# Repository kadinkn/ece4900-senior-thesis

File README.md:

# ECE4900 Floating Photovoltaic Power System

Senior Thesis project focused on designing and testing a small-scale floating photovoltaic power system with:

- Custom synchronous buck converter
- MPPT control
- STM32G474 microcontroller
- PV and battery voltage/current sensing
- Temperature sensing
- Real-time UART telemetry
- Input and output protection
- Battery charging interface

## Project Status

Current work includes:

- Buck converter power stage
- Gate driver circuitry
- 12 V auxiliary supply
- 3.3 V MCU supply
- STM32 support circuitry
- SWD programming/debug interface
- PWM control connections
- PV voltage/current sensing
- Battery voltage/current sensing
- Temperature sensing
- UART telemetry
- PV input protection
- Battery output protection

PCB layout, design-rule checks, manufacturing files, firmware, and hardware testing are still in progress.

## Main Hardware

- MCU: STM32G474CBT6TR
- Gate Driver: TI UCC27301A
- Buck MOSFETs: TI CSD18540Q5B
- PV Panel: Renogy 100 W
- Battery: Renogy 12.8 V 20 Ah LiFePO4

## Repository Files

Open the `.kicad_pro` file in KiCad to load the project.

The repository will eventually contain:

- KiCad schematic
- PCB layout
- BOM
- Datasheets/reference documents
- Manufacturing files
- Firmware
- Testing documentation

## Notes

This is a Rev 0 prototype design and is still under active development and review.

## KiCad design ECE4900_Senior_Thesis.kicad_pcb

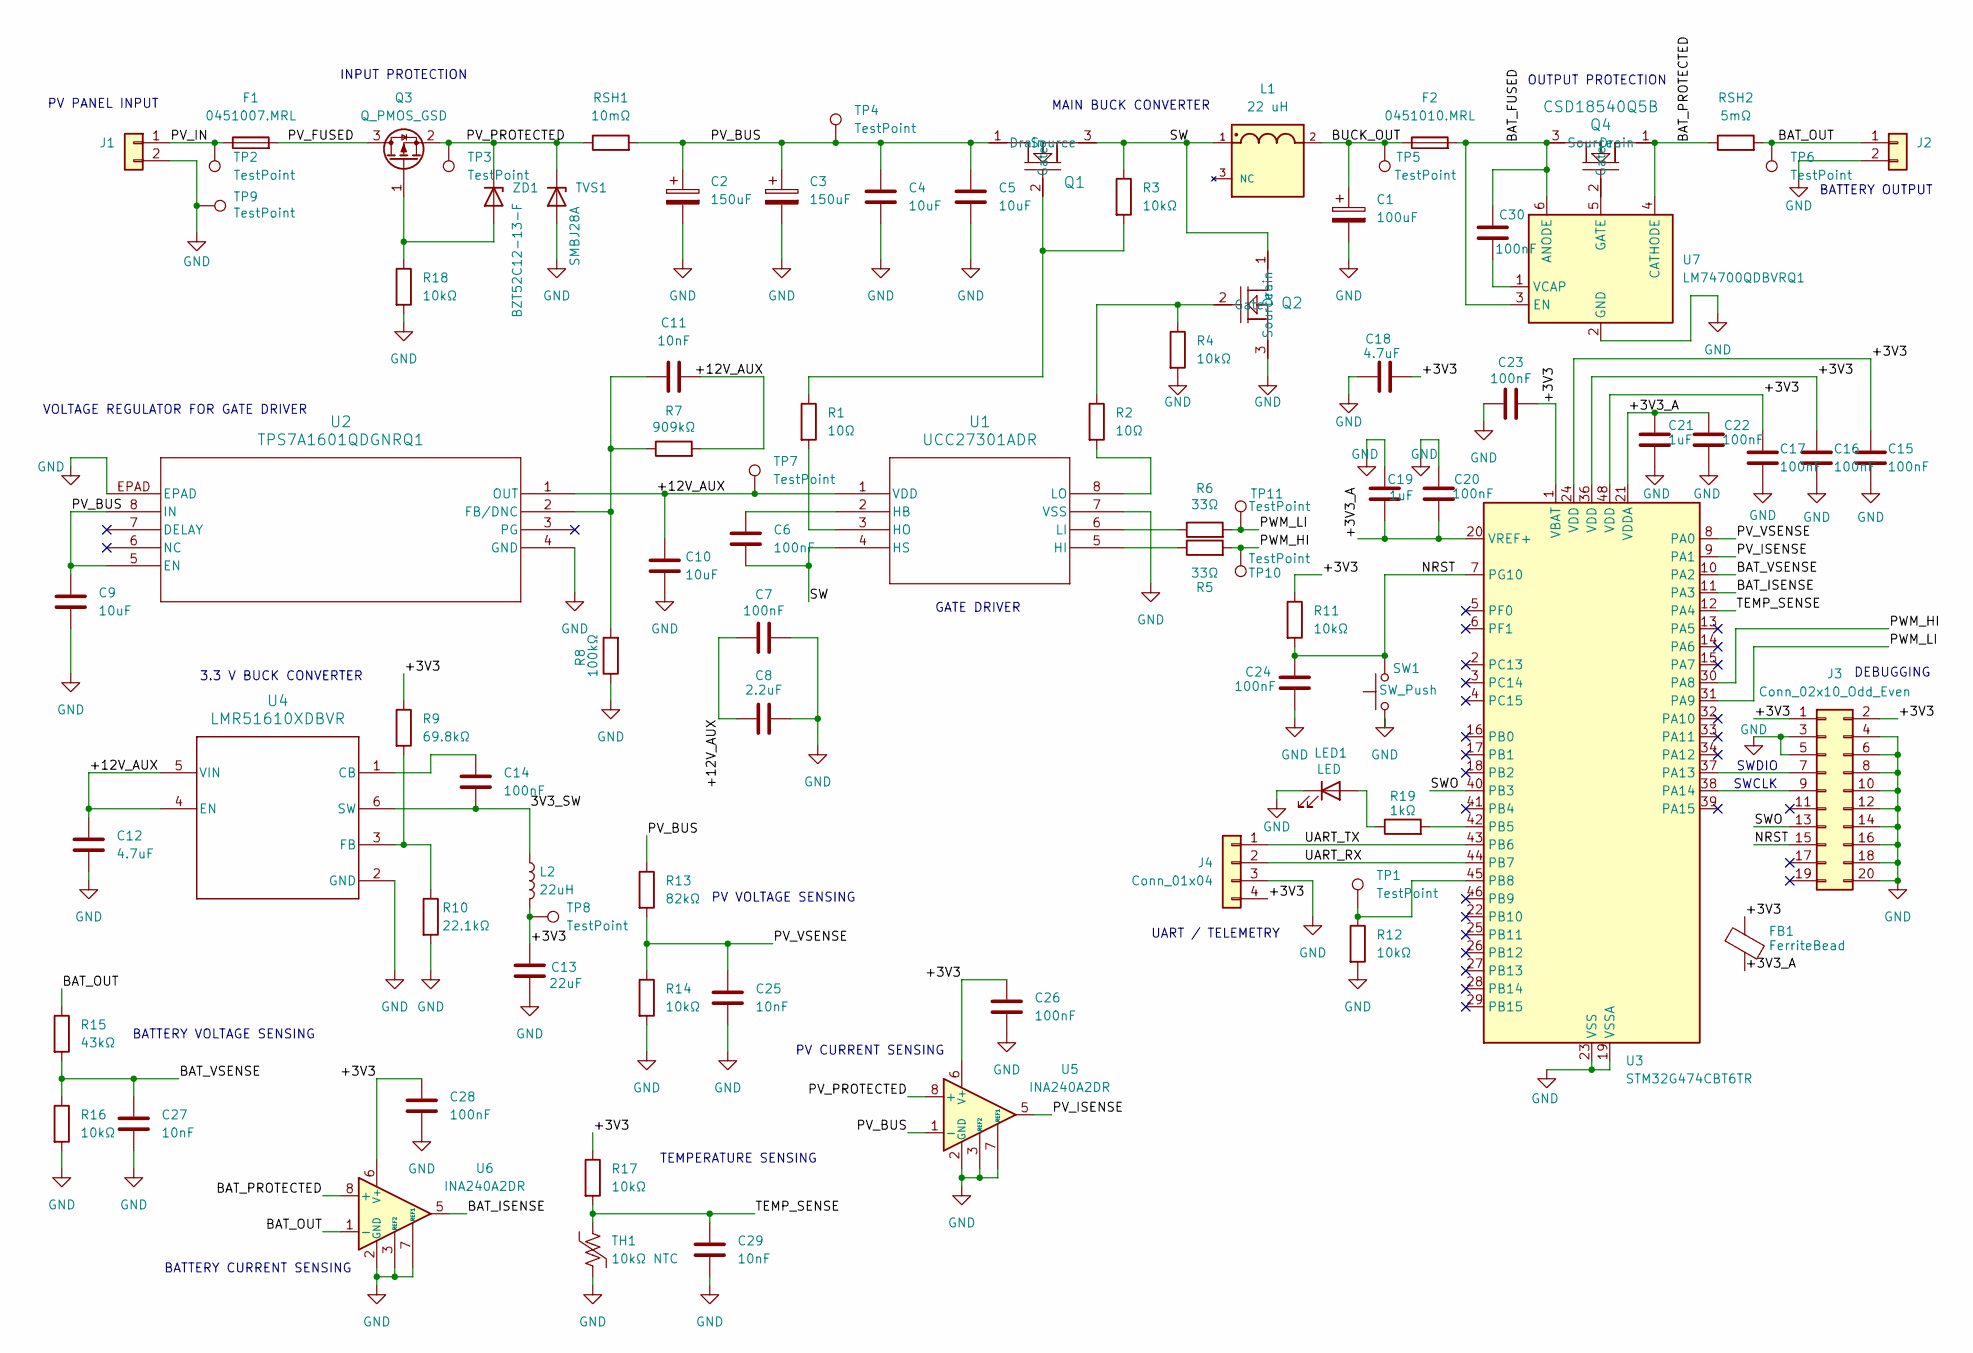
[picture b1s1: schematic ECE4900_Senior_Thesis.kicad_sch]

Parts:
C1: 100uF; CP_Elec_8x6.9
C2, C3: 150uF; CP_Elec_10x12.5
C4, C5, C9, C10: 10uF; C_1210_3225Metric
C6, C7, C14, C15, C16, C17, C20, C22, C23, C24, C26, C28, C30: 100nF; C_0603_1608Metric
C8: 2.2uF; C_0805_2012Metric
C11, C25, C27, C29: 10nF; C_0603_1608Metric
C12: 4.7uF; C_1206_3216Metric
C13: 22uF; C_1210_3225Metric
C18: 4.7uF; C_0805_2012Metric
C19, C21: 1uF; C_0603_1608Metric
F1: 0451007.MRL; Fuse_Littelfuse-NANO2-451_453
F2: 0451010.MRL; Fuse_Littelfuse-NANO2-451_453
FB1: FerriteBead; L_0603_1608Metric
J1, J2: 1757242; PhoenixContact_MSTBA_2,5_2-G-5,08_1x02_P5.08mm_Horizontal
J3: Conn_02x10_Odd_Even; IDC-Header_2x10_P2.54mm_Vertical
J4: Conn_01x04; PinHeader_1x04_P2.54mm_Vertical
L1: 22 uH; CSCF2014-220MC; PARTREV 05/31/2024
L2: 22uH; IND_1273AS-H-220M=P3
LED1: LED; LED_0603_1608Metric
Q1, Q2, Q4: CSD18540Q5B
Q3: Q_PMOS_GSD; Diodes_PowerDI3333-8
R1, R2: 10Ω; R_0805_2012Metric
R3, R4, R11, R12, R14, R16, R17, R18: 10kΩ; R_0603_1608Metric
R5, R6: 33Ω; R_0603_1608Metric
R7: 909kΩ; R_0603_1608Metric
R8: 100kΩ; R_0603_1608Metric
R9: 69.8kΩ; R_0603_1608Metric
R10: 22.1kΩ; R_0603_1608Metric
R13: 82kΩ; R_0603_1608Metric
R15: 43kΩ; R_0603_1608Metric
R19: 1kΩ; R_0603_1608Metric
RSH1: 10mΩ; KRL3264E-C-R010-F-T1
RSH2: 5mΩ; RESC6432X90N
SW1: SW_Push; SW_PUSH_6mm_H4.3mm
TH1: 10kΩ NTC; R_0603_1608Metric
TP1, TP2, TP3, TP4, TP5, TP6, TP7, TP8, TP9, TP10, TP11: TestPoint; TestPoint_Keystone_5000-5004_Miniature
TVS1: SMBJ28A; D_SMB
U1: UCC27301ADR
U2: TPS7A1601QDGNRQ1; DGN8_1P92X1P6_TEX
U3: STM32G474CBT6TR; LQFP-48_7x7mm_P0.5mm
U4: LMR51610XDBVR; DBV0006A-IPC_A
U5, U6: INA240A2DR; SOIC-8_3.9x4.9mm_P1.27mm
U7: LM74700QDBVRQ1; SOT-23-6
ZD1: BZT52C12-13-F; D_SOD-123

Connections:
/3V3_SW: C14.2, L2.1, U4.6 (SW)
/+3V3: C13.1, C15.1, C16.1, C17.1, C18.2, C23.2, C26.1, C28.1, FB1.1, J3.1, J3.2, J4.4, L2.2, R9.1, R11.1, R17.1, TP8.1 (1_1), U3.1 (VBAT), U3.24 (VDD), U3.36 (VDD), U3.48 (VDD), U5.6 (V+), U6.6 (V+)
/+3V3_A: C19.2, C20.2, C21.1, C22.1, FB1.2, U3.20 (VREF+), U3.21 (VDDA)
/+12V_AUX: C7.1, C8.1, C10.1, C11.2, C12.1, R7.2, TP7.1 (1_1), U1.1 (VDD), U2.1 (OUT), U4.4 (EN), U4.5 (VIN)
/BAT_FUSED: C30.1, F2.2, Q4.3 (Source), U7.3 (EN), U7.6 (ANODE)
/BAT_ISENSE: U3.11 (PA3), U6.5
/BAT_OUT: J2.1, R15.1, RSH2.2, TP6.1 (1_1), U6.1 (-)
/BAT_PROTECTED: Q4.1 (Drain), RSH2.1, U6.8 (+), U7.4 (CATHODE)
/BAT_VSENSE: C27.1, R15.2, R16.1, U3.10 (PA2)
/BUCK_OUT: C1.1, F2.1, L1.2, TP5.1 (1_1)
/NRST: C24.1, J3.15, R11.2, SW1.2, U3.7 (PG10)
/PV_BUS: C2.1, C3.1, C4.1, C5.1, C9.1, Q1.1 (Drain), R13.1, RSH1.2, TP4.1 (1_1), U2.5 (EN), U2.8 (IN), U5.1 (-)
/PV_FUSED: F1.2, Q3.3 (D)
/PV_IN: F1.1, J1.1, TP2.1 (1_1)
/PV_ISENSE: U3.9 (PA1), U5.5
/PV_PROTECTED: Q3.2 (S), RSH1.1, TP3.1 (1_1), TVS1.1 (K), U5.8 (+), ZD1.1 (K)
/PV_VSENSE: C25.1, R13.2, R14.1, U3.8 (PA0)
/PWM_HI: R5.2, TP10.1 (1_1), U3.30 (PA8)
/PWM_LI: R6.2, TP11.1 (1_1), U3.31 (PA9)
/SW: C6.2, L1.1, Q1.3 (Source), Q2.1 (Drain), R3.1, U1.4 (HS)
/SWO: J3.13, U3.40 (PB3)
/TEMP_SENSE: C29.1, R17.2, TH1.1, U3.12 (PA4)
/UART_RX: J4.2, U3.44 (PB7)
/UART_TX: J4.1, U3.43 (PB6)
GND: C1.2, C2.2, C3.2, C4.2, C5.2, C7.2, C8.2, C9.2, C10.2, C12.2, C13.2, C15.2, C16.2, C17.2, C18.1, C19.1, C20.1, C21.2, C22.2, C23.1, C24.2, C25.2, C26.2, C27.2, C28.2, C29.2, J1.2, J2.2, J3.3, J3.4, J3.5, J3.6, J3.8, J3.10, J3.12, J3.14, J3.16, J3.18, J3.20, J4.3, LED1.1 (K), Q2.3 (Source), R4.2, R8.1, R10.2, R12.2, R14.2, R16.2, R18.2, SW1.1, TH1.2, TP9.1 (1_1), TVS1.2 (A), U1.7 (VSS), U2.4 (GND), U2.EPAD, U3.19 (VSSA), U3.23 (VSS), U3.35 (VSS), U3.47 (VSS), U4.2 (GND), U5.2 (GND), U5.3 (REF2), U5.4 (GND), U5.7 (REF1), U6.2 (GND), U6.3 (REF2), U6.4 (GND), U6.7 (REF1), U7.2 (GND)
unnamed: J3.7, U3.37 (PA13)
unnamed: J3.9, U3.38 (PA14)
unnamed: LED1.2 (A), R19.1
unnamed: Q1.2 (Gate), R1.1, R3.2
unnamed: Q2.2 (Gate), R2.1, R4.1
unnamed: Q3.1 (G), R18.1, ZD1.2 (A)
unnamed: Q4.2 (Gate), U7.5 (GATE)
unnamed: C6.1, U1.2 (HB)
unnamed: R5.1, U1.5 (HI)
unnamed: R1.2, U1.3 (HO)
unnamed: R6.1, U1.6 (LI)
unnamed: R2.2, U1.8 (LO)
unnamed: C11.1, R7.1, R8.2, U2.2 (FB/DNC)
unnamed: R19.2, U3.42 (PB5)
unnamed: R12.1, TP1.1 (1_1), U3.45 (PB8)
unnamed: C14.1, U4.1 (CB)
unnamed: R9.2, R10.1, U4.3 (FB)
unnamed: C30.2, U7.1 (VCAP)

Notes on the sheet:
VOLTAGE REGULATOR FOR GATE DRIVER
DEBUGGING
PV VOLTAGE SENSING
PV CURRENT SENSING
PV PANEL INPUT
3.3 V BUCK CONVERTER
BATTERY CURRENT SENSING
TEMPERATURE SENSING
SWCLK
GATE DRIVER
OUTPUT PROTECTION
BATTERY VOLTAGE SENSING
BATTERY OUTPUT
MAIN BUCK CONVERTER
INPUT PROTECTION
UART / TELEMETRY
SWDIO

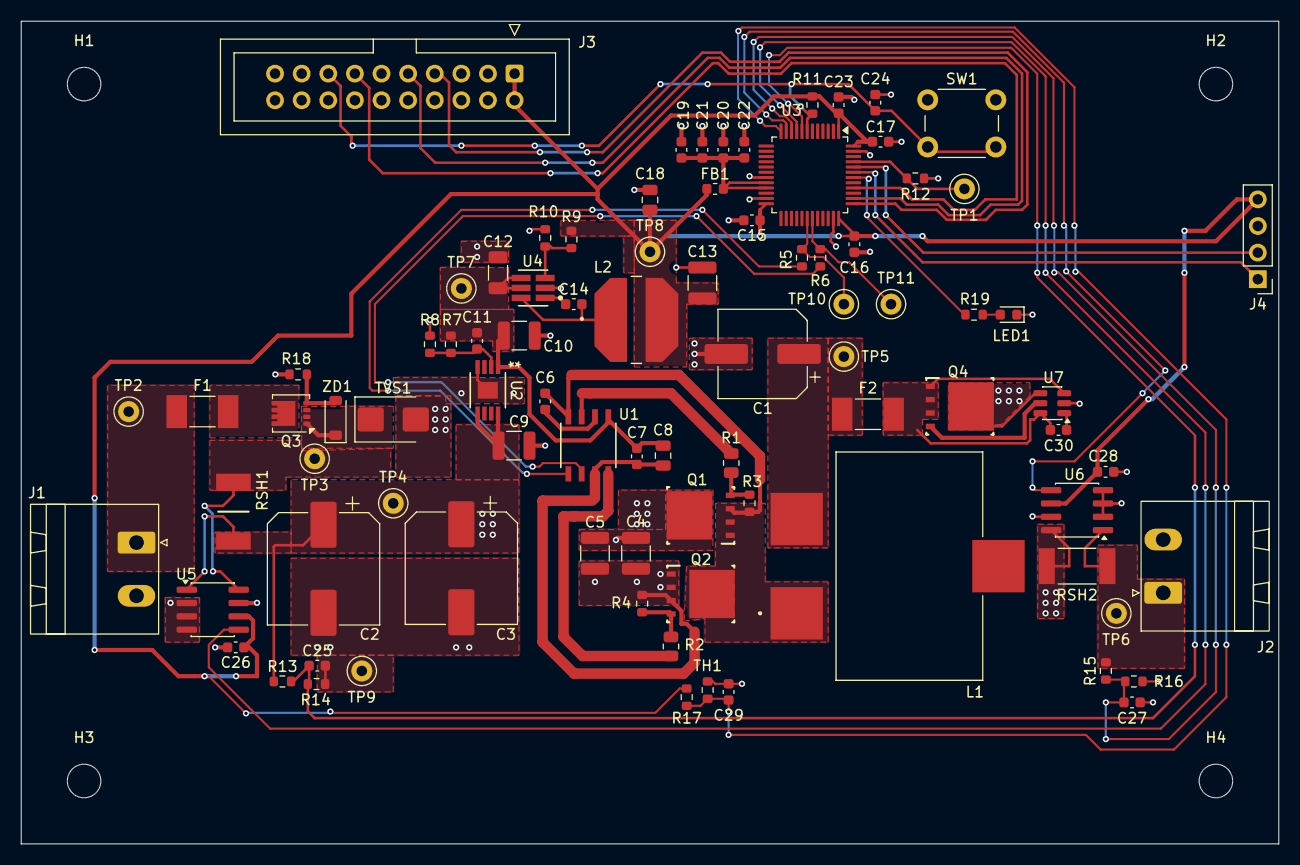
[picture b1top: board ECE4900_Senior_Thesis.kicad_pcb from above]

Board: 4 copper layers, 120.0 x 78.5 mm, 91 parts (0 on the bottom side), 43 nets.

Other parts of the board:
H1, H2, H3, H4: MountingHole_3.2mm_M3
